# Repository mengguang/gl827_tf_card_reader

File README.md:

# gl827_tf_card_reader
TF(micro SD) card reader using gl827 chip.

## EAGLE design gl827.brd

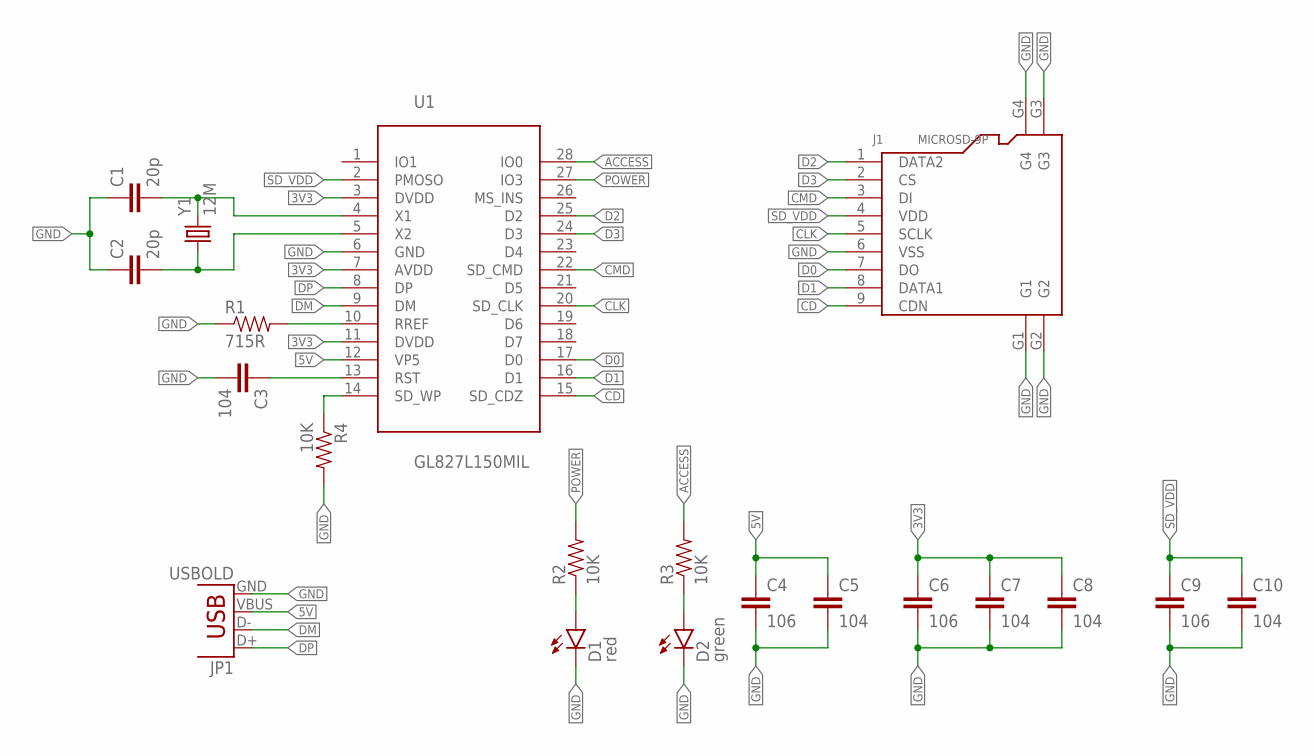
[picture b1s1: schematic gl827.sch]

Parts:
C1, C2: 20p; 0402-CAP
C3, C5, C7, C8, C10: 104; 0402-CAP
C4, C6, C9: 106; 0402-CAP
D1: red; LED-0603-EASY
D2: green; LED-0603-EASY
J1: MICROSD-9P; MICRO-SD9+4P-SMD-16.1X14.5X1.85MM
JP1: USBOLD; USB-MINIB-OLD
R1: 715R; 0603-RES
R2, R3, R4: 10K; 0402-RES
U1: GL827L150MIL; SSOP28-39
Y1: 12M; HC49US

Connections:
3V3: C6.1, C7.1, C8.1, U1.3 (DVDD), U1.7 (AVDD), U1.11 (DVDD)
5V: C4.1, C5.1, JP1.VBUS, U1.12 (VP5)
ACCESS: R3.2, U1.28 (IO0)
CD: J1.9 (CDN), U1.15 (SD_CDZ)
CLK: J1.5 (SCLK), U1.20 (SD_CLK)
CMD: J1.3 (DI), U1.22 (SD_CMD)
D0: J1.7 (DO), U1.17 (D0)
D1: J1.8 (DATA1), U1.16 (D1)
D2: J1.1 (DATA2), U1.25 (D2)
D3: J1.2 (CS), U1.24 (D3)
DM: JP1.D-, U1.9 (DM)
DP: JP1.D+, U1.8 (DP)
GND: C1.1, C2.1, C3.2, C4.2, C5.2, C6.2, C7.2, C8.2, C9.2, C10.2, D1.- (C), D2.- (C), J1.6 (VSS), J1.G1, J1.G2, J1.G3, J1.G4, JP1.GND, R1.1, R4.2, U1.6 (GND)
unnamed: C1.2, U1.4 (X1), Y1.2
unnamed: C2.2, U1.5 (X2), Y1.1
unnamed: R1.2, U1.10 (RREF)
unnamed: C3.1, U1.13 (RST)
unnamed: R4.1, U1.14 (SD_WP)
unnamed: D2.+ (A), R3.1
unnamed: D1.+ (A), R2.1
POWER: R2.2, U1.27 (IO3)
SD_VDD: C9.1, C10.1, J1.4 (VDD), U1.2 (PMOSO)

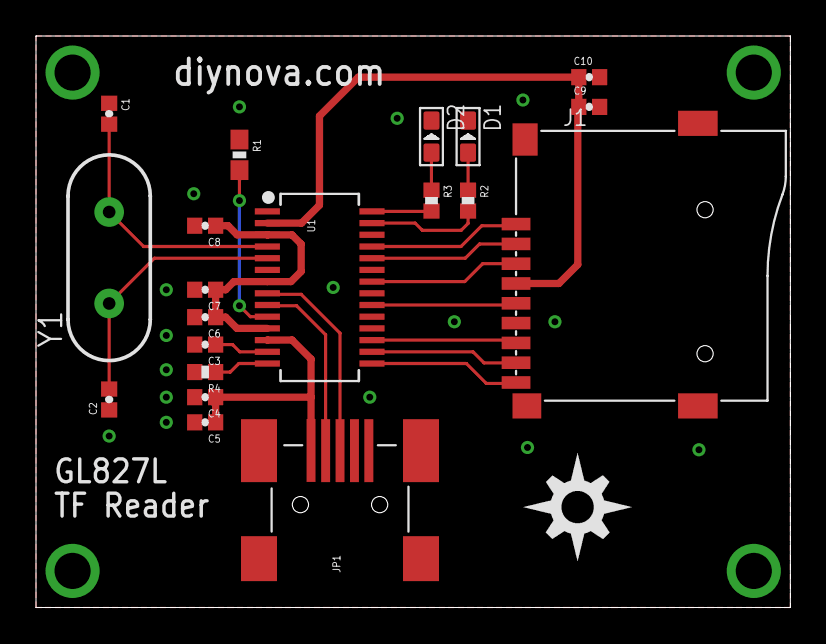
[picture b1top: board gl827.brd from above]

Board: 2 copper layers, 41.9 x 31.8 mm, 21 parts (0 on the bottom side), 22 nets.

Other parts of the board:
U$1: DIYNOVA_LOGO
